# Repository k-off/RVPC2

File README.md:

# RVPC2

Inspired by [OLIMEX RVPC](https://github.com/OLIMEX/RVPC) project, I decided to create a #higher-faster-stronger version.

Key differences:

|Feature|V1|V2|
|-|-|-|
|**MCU**|||
|Model|CH32V003F4P6|CH32X035G8R6|
|Pins|8|28|
|RAM|2k|20k|
|ROM|16k|64k|
|USB| X | **V** |
|**Display**|||
|Color|mono (1-bit)| 8 (3-bit)|
|Communication| X | **V** |
|**Ports**|||
|PS2| **V** | X |
|USB| X | **2.0 FS** |
|Audio| X | 3.5mm jack |
|Storage| X | Micro-SD |
|Power| 5V, 5mm barrel| 5V, USB-C PD|

## Build tools:

 - IDE of your choice:
   - [MounRiver](http://www.mounriver.com/download)
   - [VSCode](https://code.visualstudio.com/download)
 - Compiler (in case it isn't bundled with ide): [riscv-none-elf-gcc-xpack](https://xpack-dev-tools.github.io/riscv-none-elf-gcc-xpack/docs/install/) instructions page

## Troubleshoot

In case MounRiver build fails with `Bad CPU type in executable`, try:
 - right click on project name in project explorer (left top corner of the window)
 - select `Properties`
 - `Build Settings`->`Target Processor`->`RISC-V Compiler`: select `WCH Toolchain(GCC12)` or newer

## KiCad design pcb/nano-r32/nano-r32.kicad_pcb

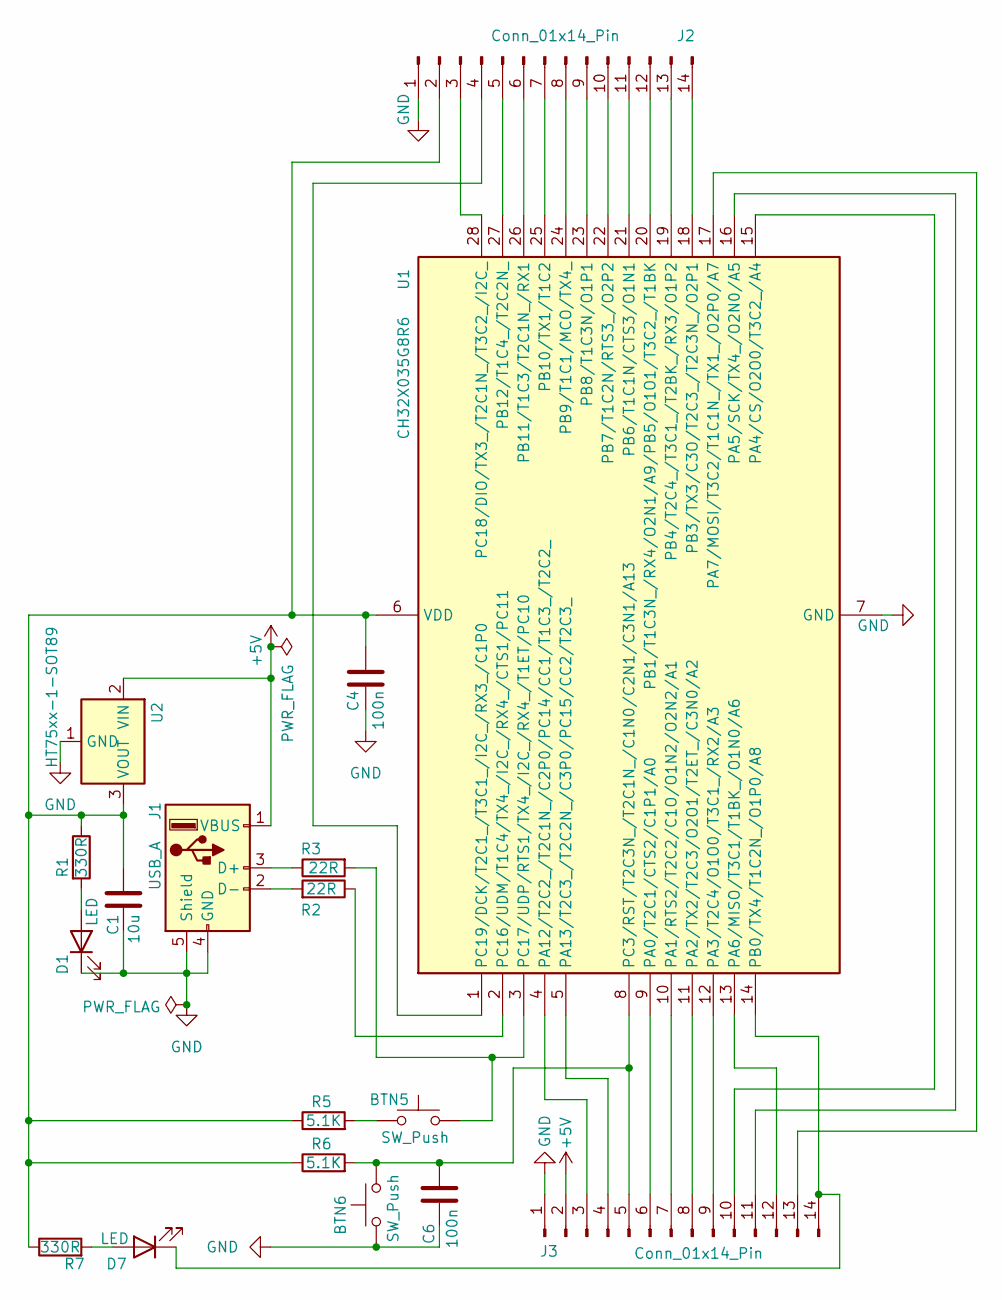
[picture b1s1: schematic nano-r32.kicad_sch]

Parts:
BTN5, BTN6: SW_Push; SW_SPST_5x5x1.5
C1: 10u; C_1206_3216Metric
C4, C6: 100n; C_1206_3216Metric
D1, D7: LED; D_1206_3216Metric
J1: USB_A; USB2_A_Female_Short_14.6x10
J2, J3: Conn_01x14_Pin; PinSocket_1x14_P2.54mm_Vertical
R1, R7: 330R; R_0805_2012Metric
R2, R3: 22R; R_0805_2012Metric
R5, R6: 5.1K; R_0805_2012Metric
U1: CH32X035G8R6; QSOP-28_3.9x9.9mm_P0.635mm
U2: HT75xx-1-SOT89; SOT-89-3

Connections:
+5V: J1.1 (VBUS), J3.2, U2.2 (VIN)
GND: BTN6.1, C1.1, C4.2, C6.2, D1.1 (K), J1.4 (GND), J1.5 (Shield), J2.1, J3.1, U1.7 (GND), U2.1 (GND)
unnamed: BTN5.1, R5.2
unnamed: D1.2 (A), R1.2
unnamed: D7.2 (A), R7.2
unnamed: D7.1 (K), J3.14, U1.14 (PB0/TX4/T1C2N_/O1P0/A8)
unnamed: J1.3 (D+), R3.1
unnamed: J1.2 (D-), R2.2
unnamed: C1.2, C4.1, J2.2, R1.1, R5.1, R6.1, R7.1, U1.6 (VDD), U2.3 (VOUT)
unnamed: J2.3, U1.28 (PC18/DIO/TX3_/T2C1N_/T3C2_/I2C_)
unnamed: J2.4, U1.1 (PC19/DCK/T2C1_/T3C1_/I2C_/RX3_/C1P0)
unnamed: J2.5, U1.27 (PB12/T1C4_/T2C2N_)
unnamed: J2.6, U1.26 (PB11/T1C3/T2C1N_/RX1)
unnamed: J2.7, U1.25 (PB10/TX1/T1C2)
unnamed: J2.8, U1.24 (PB9/T1C1/MCO/TX4_)
unnamed: J2.9, U1.23 (PB8/T1C3N/O1P1)
unnamed: J2.10, U1.22 (PB7/T1C2N/RTS3_/O2P2)
unnamed: J2.11, U1.21 (PB6/T1C1N/CTS3/O1N1)
unnamed: J2.12, U1.20 (PB1/T1C3N_/RX4/O2N1/A9/PB5/O1O1/T3C2_/T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)
unnamed: J2.13, U1.19 (PB4/T2C4_/T3C1_/T2BK_/RX3/O1P2)
unnamed: J2.14, U1.18 (PB3/TX3/C3O/T2C3_/T2C3N_/O2P1)
unnamed: J3.3, U1.4 (PA12/T2C2_/T2C1N_/C2P0/PC14/CC1/T1C3_/T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)
unnamed: J3.4, U1.5 (PA13/T2C3_/T2C2N_/C3P0/PC15/CC2/T2C3_)
unnamed: BTN6.2, C6.1, J3.5, R6.2, U1.8 (PC3/RST/T2C3N_/T2C1N_/C1N0/C2N1/C3N1/A13)
unnamed: J3.6, U1.9 (PA0/T2C1/CTS2/C1P1/A0)
unnamed: J3.7, U1.10 (PA1/RTS2/T2C2/C1O/O1N2/O2N2/A1)
unnamed: J3.8, U1.11 (PA2/TX2/T2C3/O2O1/T2ET_/C3N0/A2)
unnamed: J3.9, U1.12 (PA3/T2C4/O1O0/T3C1_/RX2/A3)
unnamed: J3.10, U1.15 (PA4/CS/O2O0/T3C2_/A4)
unnamed: J3.11, U1.16 (PA5/SCK/TX4_/O2N0/A5)
unnamed: J3.12, U1.13 (PA6/MISO/T3C1/T1BK_/O1N0/A6)
unnamed: J3.13, U1.17 (PA7/MOSI/T3C2/T1C1N_/TX1_/O2P0/A7)
unnamed: R2.1, U1.2 (PC16/UDM/T1C4/TX4_/I2C_/RX4_/CTS1/PC11)
unnamed: BTN5.2, R3.2, U1.3 (PC17/UDP/RTS1/TX4_/I2C_/RX4_/T1ET/PC10)

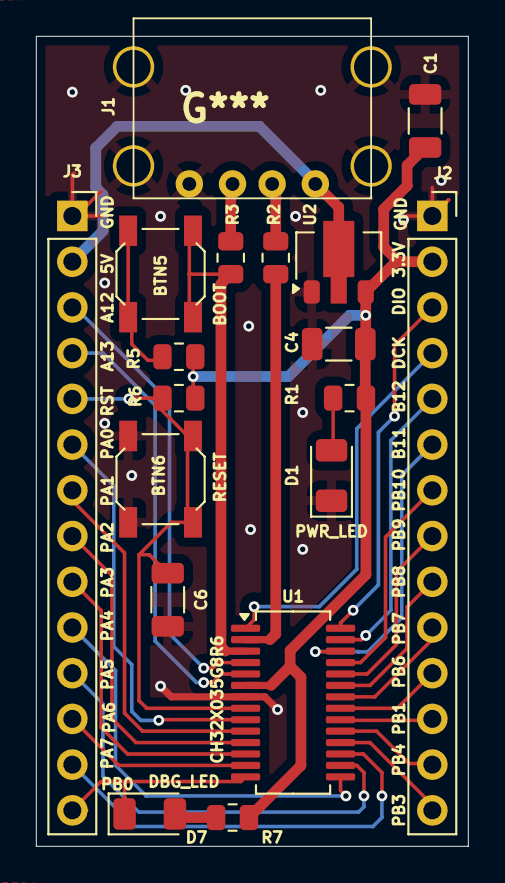
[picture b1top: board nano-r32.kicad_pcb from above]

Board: 2 copper layers, 24.0 x 45.0 mm, 18 parts (0 on the bottom side), 34 nets.

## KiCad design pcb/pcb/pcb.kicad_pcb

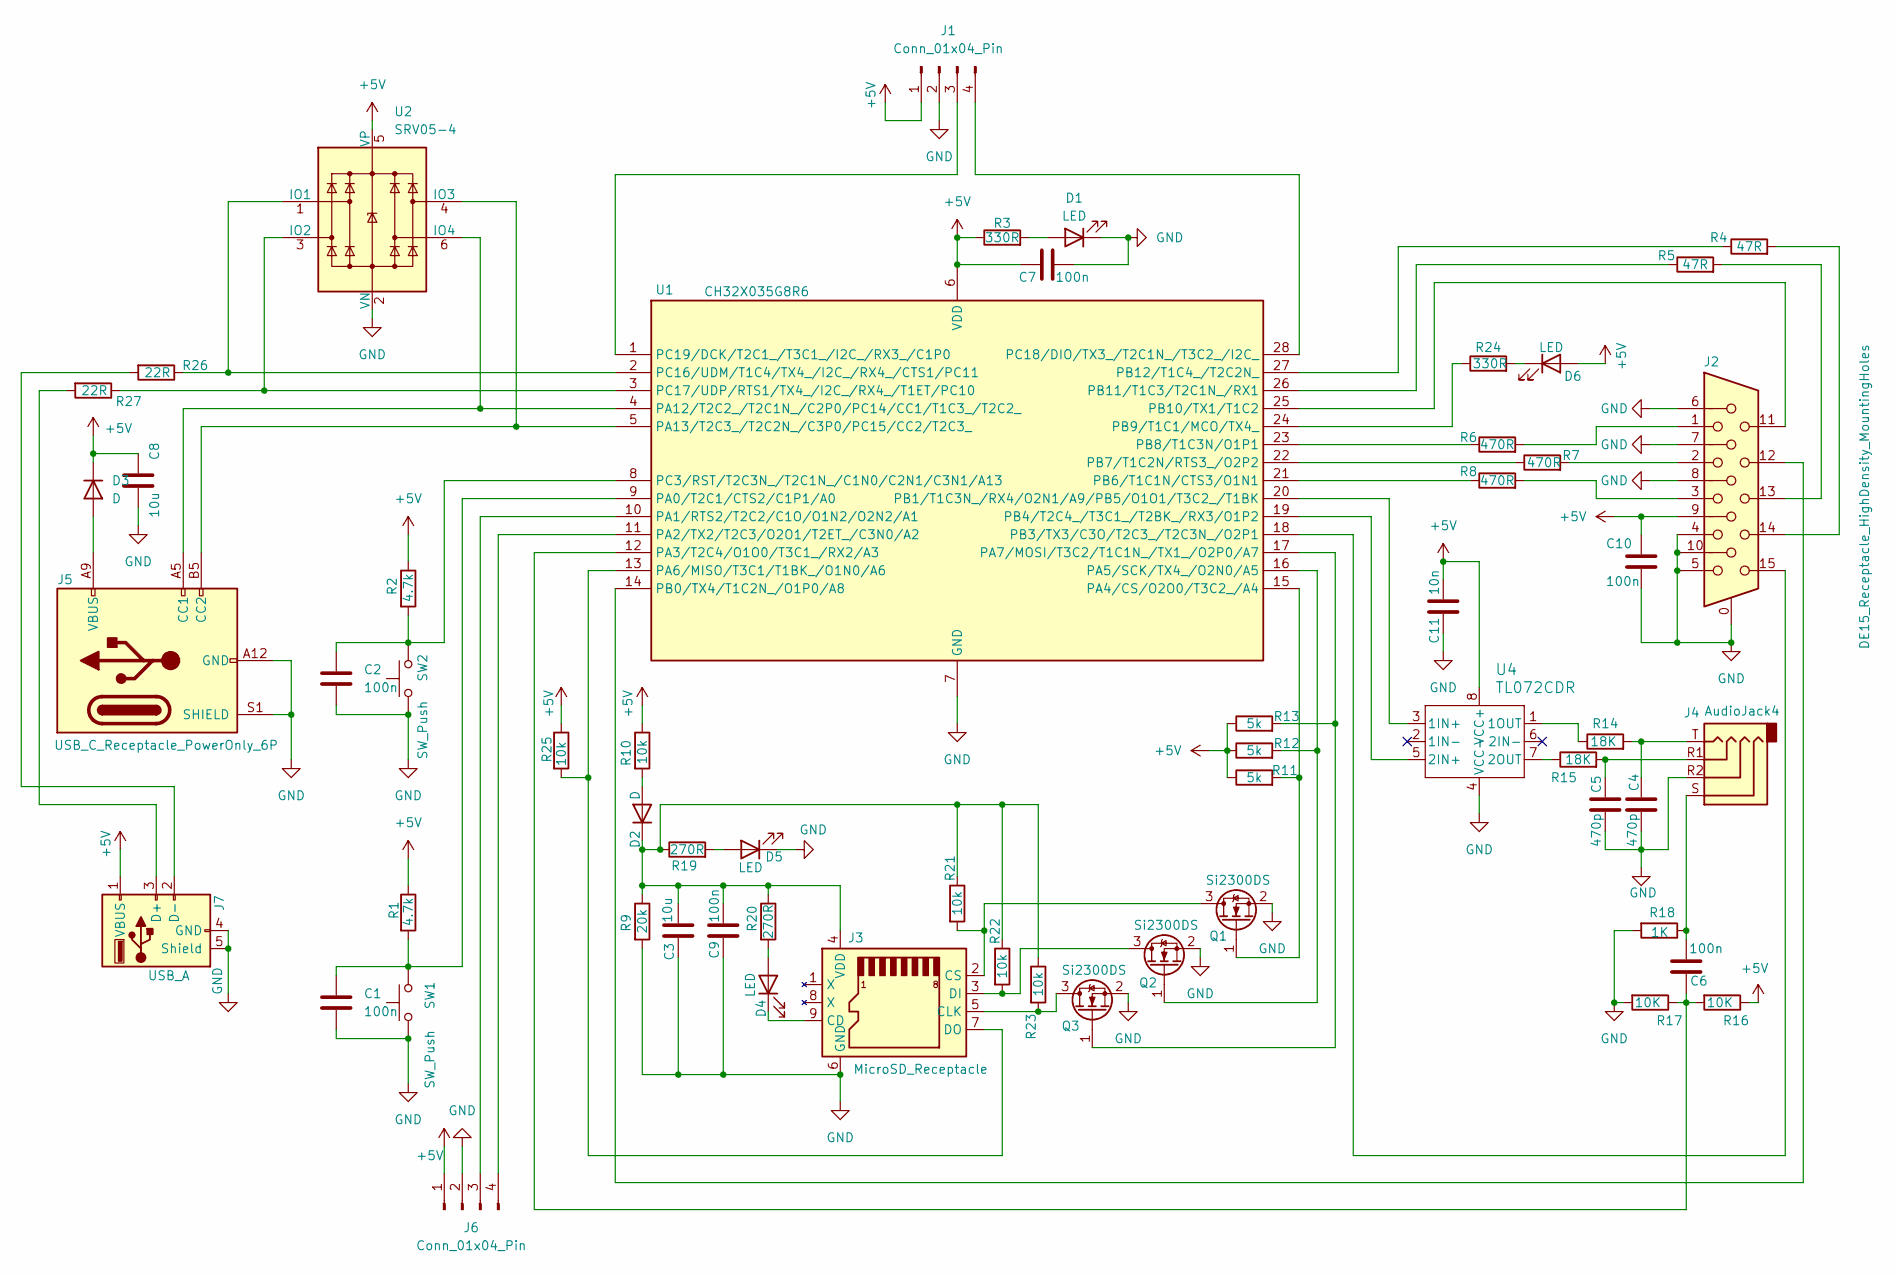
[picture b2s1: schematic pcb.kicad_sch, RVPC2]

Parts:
C1, C2, C6, C7, C9, C10: 100n; C_1206_3216Metric
C3, C8: 10u; C_1206_3216Metric
C4, C5: 470p; C_1206_3216Metric
C11: 10n; C_1206_3216Metric
D1, D4, D5, D6: LED; LED_1206_3216Metric
D2, D3: D; D_1206_3216Metric
J1, J6: Conn_01x04_Pin; PinHeader_1x04_P2.54mm_Vertical
J2: DE15_Receptacle_HighDensity_MountingHoles; DSUB-15-HD_Female_Vertical_P2.29x1.98mm_MountingHoles
J3: MicroSD_Receptacle; Micro_SD_9pin_push_push
J4: AudioJack4; Jack_3.5mm_PJ320E_Horizontal
J5: USB_C_Receptacle_PowerOnly_6P; USB_C_Receptacle_HRO_TYPE-C-31-M-17
J7: USB_A; USB2_A_Female_Short_14.6x10
Q1, Q2, Q3: Si2300DS; SOT-23
R1, R2: 4.7k; R_0805_2012Metric
R3, R24: 330R; R_0805_2012Metric
R4, R5: 47R; R_0805_2012Metric
R6, R7, R8: 470R; R_0805_2012Metric
R9: 20k; R_0805_2012Metric
R10, R21, R22, R23, R25: 10k; R_0805_2012Metric
R11, R12, R13: 5k; R_0805_2012Metric
R14, R15: 18K; R_0805_2012Metric
R16, R17: 10K; R_0805_2012Metric
R18: 1K; R_0805_2012Metric
R19, R20: 270R; R_0805_2012Metric
R26, R27: 22R; R_0805_2012Metric
SW1, SW2: SW_Push; SW_SPST_5x5_4pin
U1: CH32X035G8R6; QSOP-28_3.9x9.9mm_P0.635mm
U2: SRV05-4; SOT-23-6
U4: TL072CDR; D8

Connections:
+5V: C7.1, C8.1, C10.1, C11.1, D3.1 (K), D6.2 (A), J1.1, J2.9, J6.1, J7.1 (VBUS), R1.1, R2.1, R3.1, R10.1, R11.1, R12.1, R13.1, R16.1, R25.1, U1.6 (VDD), U2.5 (VP), U4.8 (VCC+)
GND: C1.2, C2.2, C3.2, C4.2, C5.2, C7.2, C8.2, C9.2, C10.2, C11.2, D1.1 (K), D5.1 (K), J1.2, J2.0, J2.4, J2.5, J2.6, J2.7, J2.8, J2.10, J3.6 (GND), J4.R2, J5.A12 (GND), J5.B12 (GND), J5.S1 (SHIELD), J6.2, J7.4 (GND), J7.5 (Shield), Q1.2 (S), Q2.2 (S), Q3.2 (S), R9.2, R17.2, R18.2, SW1.1, SW2.1, U1.7 (GND), U2.2 (VN), U4.4 (VCC-)
unnamed: C4.1, J4.T, R14.2
unnamed: C5.1, J4.R1, R15.2
unnamed: C6.1, J4.S, R18.1
unnamed: D1.2 (A), R3.2
unnamed: D2.2 (A), R10.2
unnamed: C3.1, C9.1, D2.1 (K), J3.4 (VDD), R9.1, R19.1, R20.1, R21.1, R22.1, R23.1
unnamed: D3.2 (A), J5.A9 (VBUS), J5.B9 (VBUS)
unnamed: D4.2 (A), R20.2
unnamed: D4.1 (K), J3.9 (CD)
unnamed: D5.2 (A), R19.2
unnamed: D6.1 (K), R24.2
unnamed: J1.3, U1.1 (PC19/DCK/T2C1_/T3C1_/I2C_/RX3_/C1P0)
unnamed: J1.4, U1.28 (PC18/DIO/TX3_/T2C1N_/T3C2_/I2C_)
unnamed: J2.1, R6.2
unnamed: J2.2, R7.2
unnamed: J2.3, R8.2
unnamed: J2.13, R5.2
unnamed: J2.14, R4.2
unnamed: J3.5 (CLK), Q3.3 (D), R23.2
unnamed: J3.2 (CS), Q1.3 (D), R21.2
unnamed: J3.3 (DI), Q2.3 (D), R22.2
unnamed: J3.7 (DO), R25.2, U1.13 (PA6/MISO/T3C1/T1BK_/O1N0/A6)
unnamed: J5.A5 (CC1), U1.4 (PA12/T2C2_/T2C1N_/C2P0/PC14/CC1/T1C3_/T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), U2.6 (IO4)
unnamed: J5.B5 (CC2), U1.5 (PA13/T2C3_/T2C2N_/C3P0/PC15/CC2/T2C3_), U2.4 (IO3)
unnamed: J6.3, U1.10 (PA1/RTS2/T2C2/C1O/O1N2/O2N2/A1)
unnamed: J6.4, U1.11 (PA2/TX2/T2C3/O2O1/T2ET_/C3N0/A2)
unnamed: J7.3 (D+), R27.2
unnamed: J7.2 (D-), R26.2
unnamed: Q1.1 (G), R11.2, U1.15 (PA4/CS/O2O0/T3C2_/A4)
unnamed: Q2.1 (G), R12.2, U1.16 (PA5/SCK/TX4_/O2N0/A5)
unnamed: Q3.1 (G), R13.2, U1.17 (PA7/MOSI/T3C2/T1C1N_/TX1_/O2P0/A7)
unnamed: C1.1, R1.2, SW1.2, U1.9 (PA0/T2C1/CTS2/C1P1/A0)
unnamed: C6.2, R16.2, R17.1, U1.12 (PA3/T2C4/O1O0/T3C1_/RX2/A3)
unnamed: J2.12, U1.14 (PB0/TX4/T1C2N_/O1P0/A8)
unnamed: U1.20 (PB1/T1C3N_/RX4/O2N1/A9/PB5/O1O1/T3C2_/T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), U4.3 (1IN+)
unnamed: J2.15, U1.18 (PB3/TX3/C3O/T2C3_/T2C3N_/O2P1)
unnamed: U1.19 (PB4/T2C4_/T3C1_/T2BK_/RX3/O1P2), U4.5 (2IN+)
unnamed: R8.1, U1.21 (PB6/T1C1N/CTS3/O1N1)
unnamed: R7.1, U1.22 (PB7/T1C2N/RTS3_/O2P2)
unnamed: R6.1, U1.23 (PB8/T1C3N/O1P1)
unnamed: R24.1, U1.24 (PB9/T1C1/MCO/TX4_)
unnamed: J2.11, U1.25 (PB10/TX1/T1C2)
unnamed: R5.1, U1.26 (PB11/T1C3/T2C1N_/RX1)
unnamed: R4.1, U1.27 (PB12/T1C4_/T2C2N_)
unnamed: C2.1, R2.2, SW2.2, U1.8 (PC3/RST/T2C3N_/T2C1N_/C1N0/C2N1/C3N1/A13)
unnamed: R26.1, U1.2 (PC16/UDM/T1C4/TX4_/I2C_/RX4_/CTS1/PC11), U2.1 (IO1)
unnamed: R27.1, U1.3 (PC17/UDP/RTS1/TX4_/I2C_/RX4_/T1ET/PC10), U2.3 (IO2)
unnamed: R14.1, U4.1 (1OUT)
unnamed: R15.1, U4.7 (2OUT)

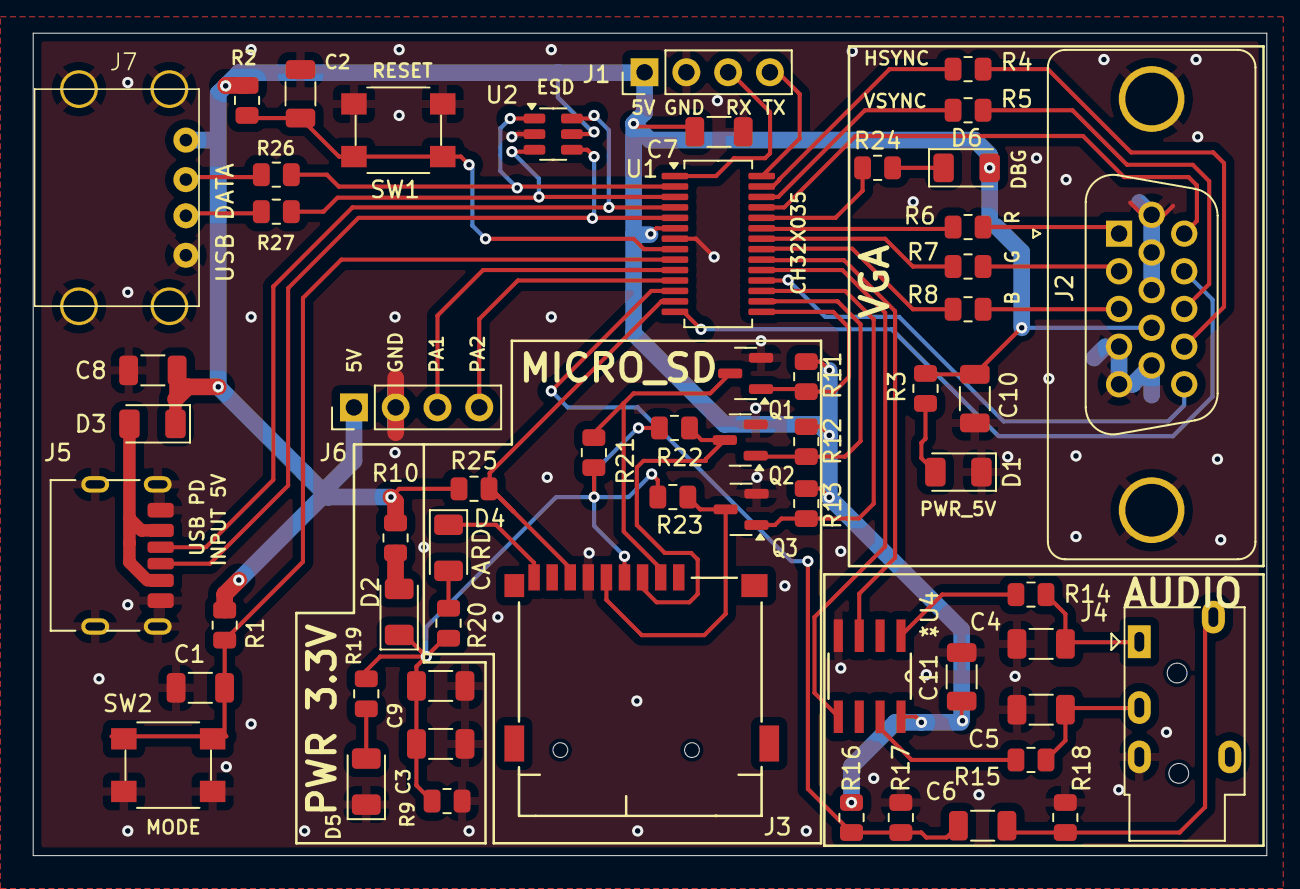
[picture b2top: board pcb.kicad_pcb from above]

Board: 2 copper layers, 75.0 x 50.0 mm, 59 parts (0 on the bottom side), 51 nets.

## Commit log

2025-01-06 ch32x035 docs and examples
2025-01-06 cleanup
2025-01-06 updage gitignore
2025-01-07 add kicad ch32x035 library
    update GPIO toolchain gcc version to 12
2025-01-08 kicad library: fall back to standard footprints
2025-01-08 cleanup kicad library
2025-01-08 adhere 'ki_fp_filters' values to kicad guidelines
2025-01-08 update 'ki_keywords'
2025-01-08 adhere to kicad library guidelines
2025-01-28 add kicad TL072CDR symbol and footprint
2025-01-28 add kicad pcb templates
2025-01-28 update CH32X035 kicad lib
2025-01-28 update gitignore
2025-01-28 update board
2025-02-23 add audio jack
2025-02-23 update code examples settings
2025-02-23 update schematic and pcb
2025-02-23 update pcb
2025-02-23 add image
2025-03-08 add arduino-like debug board for CH32X035 mcu
2025-03-08 update rvpc2 pcb
2025-03-28 update debug board schematic and layout: add boot button, fix led polarity
